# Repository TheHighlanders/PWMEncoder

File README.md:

# A Custom PWM Encoder for FRC
This encoder connects to a SparkMAX Motor Controller, using the Data Port. This encoder was designed with use on Swerve Drive Specialties Mk 4 Modules, with NEOs. 

These utilize the AS5047 chip to read a rotating magnetic field, and convert that to a PWM output.

Included in this repo are the KiCAD project files, as well as STEP file for the board, and 2 parts of a case that we used to mount these encoders.

## Important Notes

### Data Port Connector
In the project files, the Data Port connector is included on the incorrect side of the board. The pinouts for the board are correct, the only change that needs to be made if you use these is in assembly, the connector should be mounted on the top side (with the LED) of the board, and the notch should face away from the encoder IC.

### Programming the IC
The AS5047 encoder used here requires a programming process to output a PWM signal. A script to do this via an Arduino can be found here: [Programming Script](https://github.com/TheHighlanders/AS5047ProgrammingScript)

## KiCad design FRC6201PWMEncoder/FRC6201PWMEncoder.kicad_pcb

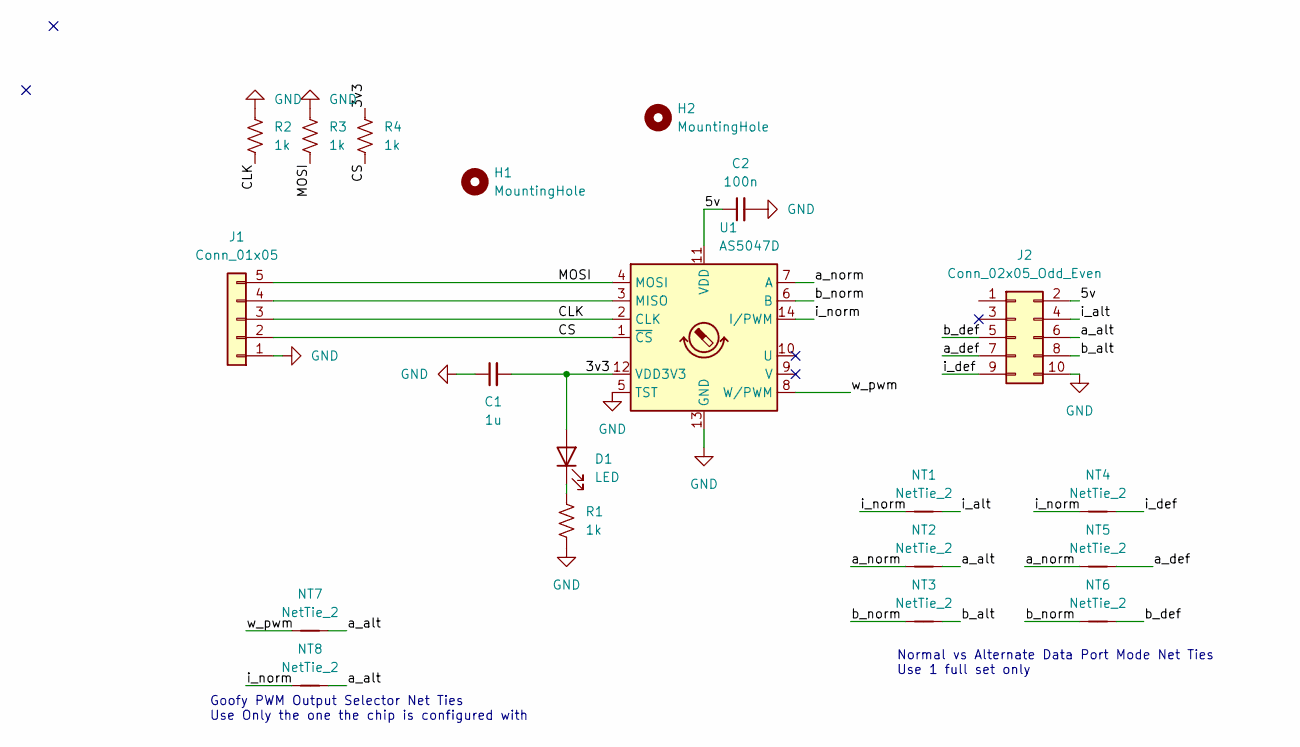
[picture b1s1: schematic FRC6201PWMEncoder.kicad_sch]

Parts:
C1: 1u; C_0603_1608Metric_Pad1.08x0.95mm_HandSolder
C2: 100n; C_0603_1608Metric_Pad1.08x0.95mm_HandSolder
D1: LED; LED_0603_1608Metric_Pad1.05x0.95mm_HandSolder
H1, H2: MountingHole; MountingHole_2.2mm_M2
J1: Conn_01x05; PinHeader_1x05_P1.27mm_Vertical
J2: Conn_02x05_Odd_Even; PinSocket_2x05_P1.27mm_Vertical
NT1, NT2, NT3, NT4, NT5, NT6, NT7, NT8: NetTie_2; Jumper
R1, R2, R3, R4: 1k; R_0603_1608Metric_Pad0.98x0.95mm_HandSolder
U1: AS5047D; TSSOP-14_4.4x5mm_P0.65mm

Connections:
/3v3: C1.2, D1.2 (A), R4.1, U1.12 (VDD3V3)
/5v: C2.1, J2.2, U1.11 (VDD)
/CLK: J1.3, R2.2, U1.2 (CLK)
/CS: J1.2, R4.2, U1.1 (~CS)
/MOSI: J1.5, R3.2, U1.4 (MOSI)
/a_alt: J2.6, NT2.2, NT7.2, NT8.2
/a_def: J2.7, NT5.2
/a_norm: NT2.1, NT5.1, U1.7 (A)
/b_alt: J2.8, NT3.2
/b_def: J2.5, NT6.2
/b_norm: NT3.1, NT6.1, U1.6 (B)
/i_alt: J2.4, NT1.2
/i_def: J2.9, NT4.2
/i_norm: NT1.1, NT4.1, NT8.1, U1.14 (I/PWM)
/w_pwm: NT7.1, U1.8 (W/PWM)
GND: C1.1, C2.2, J1.1, J2.10, R1.2, R2.1, R3.1, U1.5 (TST), U1.13 (GND)
unnamed: D1.1 (K), R1.1
unnamed: J1.4, U1.3 (MISO)

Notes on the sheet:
Goofy PWM Output Selector Net Ties Use Only the one the chip is configured with
Normal vs Alternate Data Port Mode Net Ties Use 1 full set only

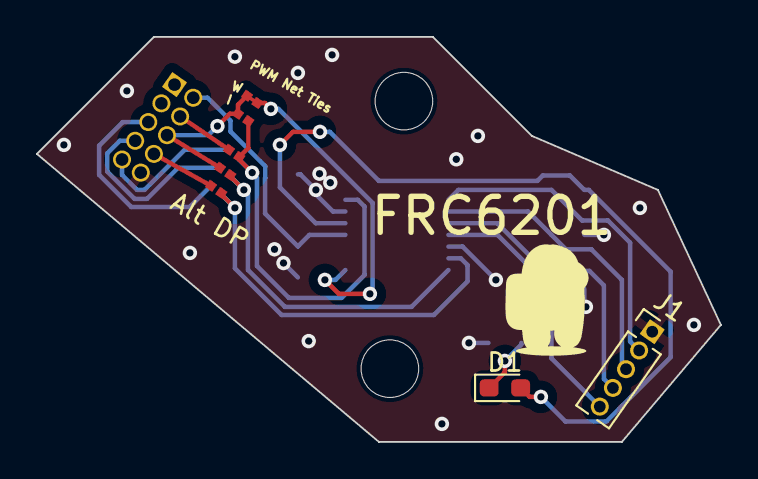
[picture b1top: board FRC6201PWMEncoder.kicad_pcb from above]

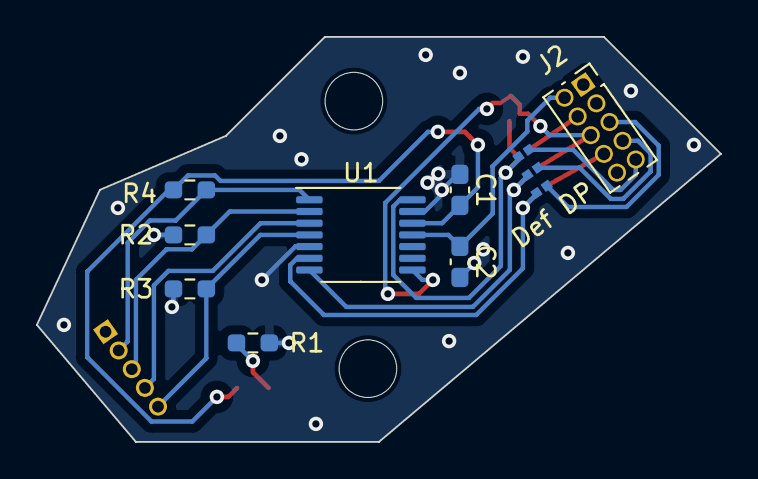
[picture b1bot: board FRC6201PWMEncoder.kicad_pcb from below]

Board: 2 copper layers, 38.0 x 22.5 mm, 18 parts (11 on the bottom side), 18 nets.

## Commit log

2023-11-08 Added Encoder Files
2023-11-15 Increased Hole size to M3
2024-01-07 Extra Files?
